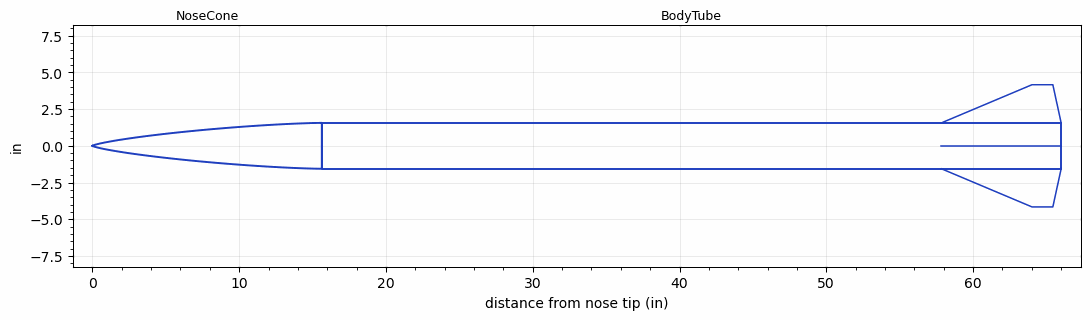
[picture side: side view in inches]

<RASAeroDocument>
 <FileVersion>2</FileVersion>
 <RocketDesign>
  <NoseCone>
   <Length>15.6299</Length>
   <Diameter>3.126</Diameter>
   <Shape>Von Karman Ogive</Shape>
   <Location>0</Location>
  </NoseCone>
  <BodyTube>
   <Length>50.37</Length>
   <Diameter>3.126</Diameter>
   <LaunchLugDiameter>0.5</LaunchLugDiameter>
   <LaunchLugLength>1</LaunchLugLength>
   <Location>15.6299</Location>
   <Fin>
    <Count>4</Count>
    <Chord>8.1575</Chord>
    <Span>2.6008</Span>
    <SweepDistance>6.1732</SweepDistance>
    <TipChord>1.4173</TipChord>
    <Thickness>0.4</Thickness>
    <LERadius>0.0787</LERadius>
    <Location>8.1575</Location>
    <AirfoilSection>Hexagonal</AirfoilSection>
    <FX1>1.5</FX1>
    <FX3>1.5</FX3>
   </Fin>
  </BodyTube>
  <Surface>Smooth Paint</Surface>
  <ModifiedBarrowman>False</ModifiedBarrowman>
  <Turbulence>False</Turbulence>
  <UseBooster1>False</UseBooster1>
  <UseBooster2>False</UseBooster2>
 </RocketDesign>
 <LaunchSite>
  <Altitude>0</Altitude>
  <Pressure>0</Pressure>
  <RodAngle>0</RodAngle>
  <RodLength>40</RodLength>
  <Temperature>64</Temperature>
  <WindSpeed>70</WindSpeed>
 </LaunchSite>
 <Recovery>
  <Altitude1>1000</Altitude1>
  <Altitude2>1000</Altitude2>
  <DeviceType1>Parachute</DeviceType1>
  <DeviceType2>None</DeviceType2>
  <Event1>True</Event1>
  <Event2>False</Event2>
  <Size1>40</Size1>
  <Size2>1</Size2>
  <EventType1>Apogee</EventType1>
  <EventType2>None</EventType2>
  <CD1>1.33</CD1>
  <CD2>1.33</CD2>
 </Recovery>
 <SimulationList>
  <Simulation>
   <SustainerEngine>L2375-WT  (CTI)</SustainerEngine>
   <SustainerLaunchWt>16.77</SustainerLaunchWt>
   <SustainerNozzleDiameter>3.123</SustainerNozzleDiameter>
   <SustainerCG>47.67</SustainerCG>
   <SustainerIgnitionDelay>0</SustainerIgnitionDelay>
   <Booster1SeparationDelay>0</Booster1SeparationDelay>
   <Booster1IgnitionDelay>0</Booster1IgnitionDelay>
   <IncludeBooster1>False</IncludeBooster1>
   <Booster2Delay>0</Booster2Delay>
   <IncludeBooster2>False</IncludeBooster2>
   <TimetoApogee>26.91052</TimetoApogee>
   <MaxAltitude>16605.86</MaxAltitude>
   <MaxVelocity>2192.238</MaxVelocity>
   <OptimumWt>14.52</OptimumWt>
   <OptimumMaxAlt>14.52</OptimumMaxAlt>
  </Simulation>
 </SimulationList>
</RASAeroDocument>
